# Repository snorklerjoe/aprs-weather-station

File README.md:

# aprs-weather-station
An APRS weather station with a transmitter designed from scratch

_(Slideshow with more info)_

For more information, see my [blog](https://www.hosticlefifer.com/blog/?show=14)!

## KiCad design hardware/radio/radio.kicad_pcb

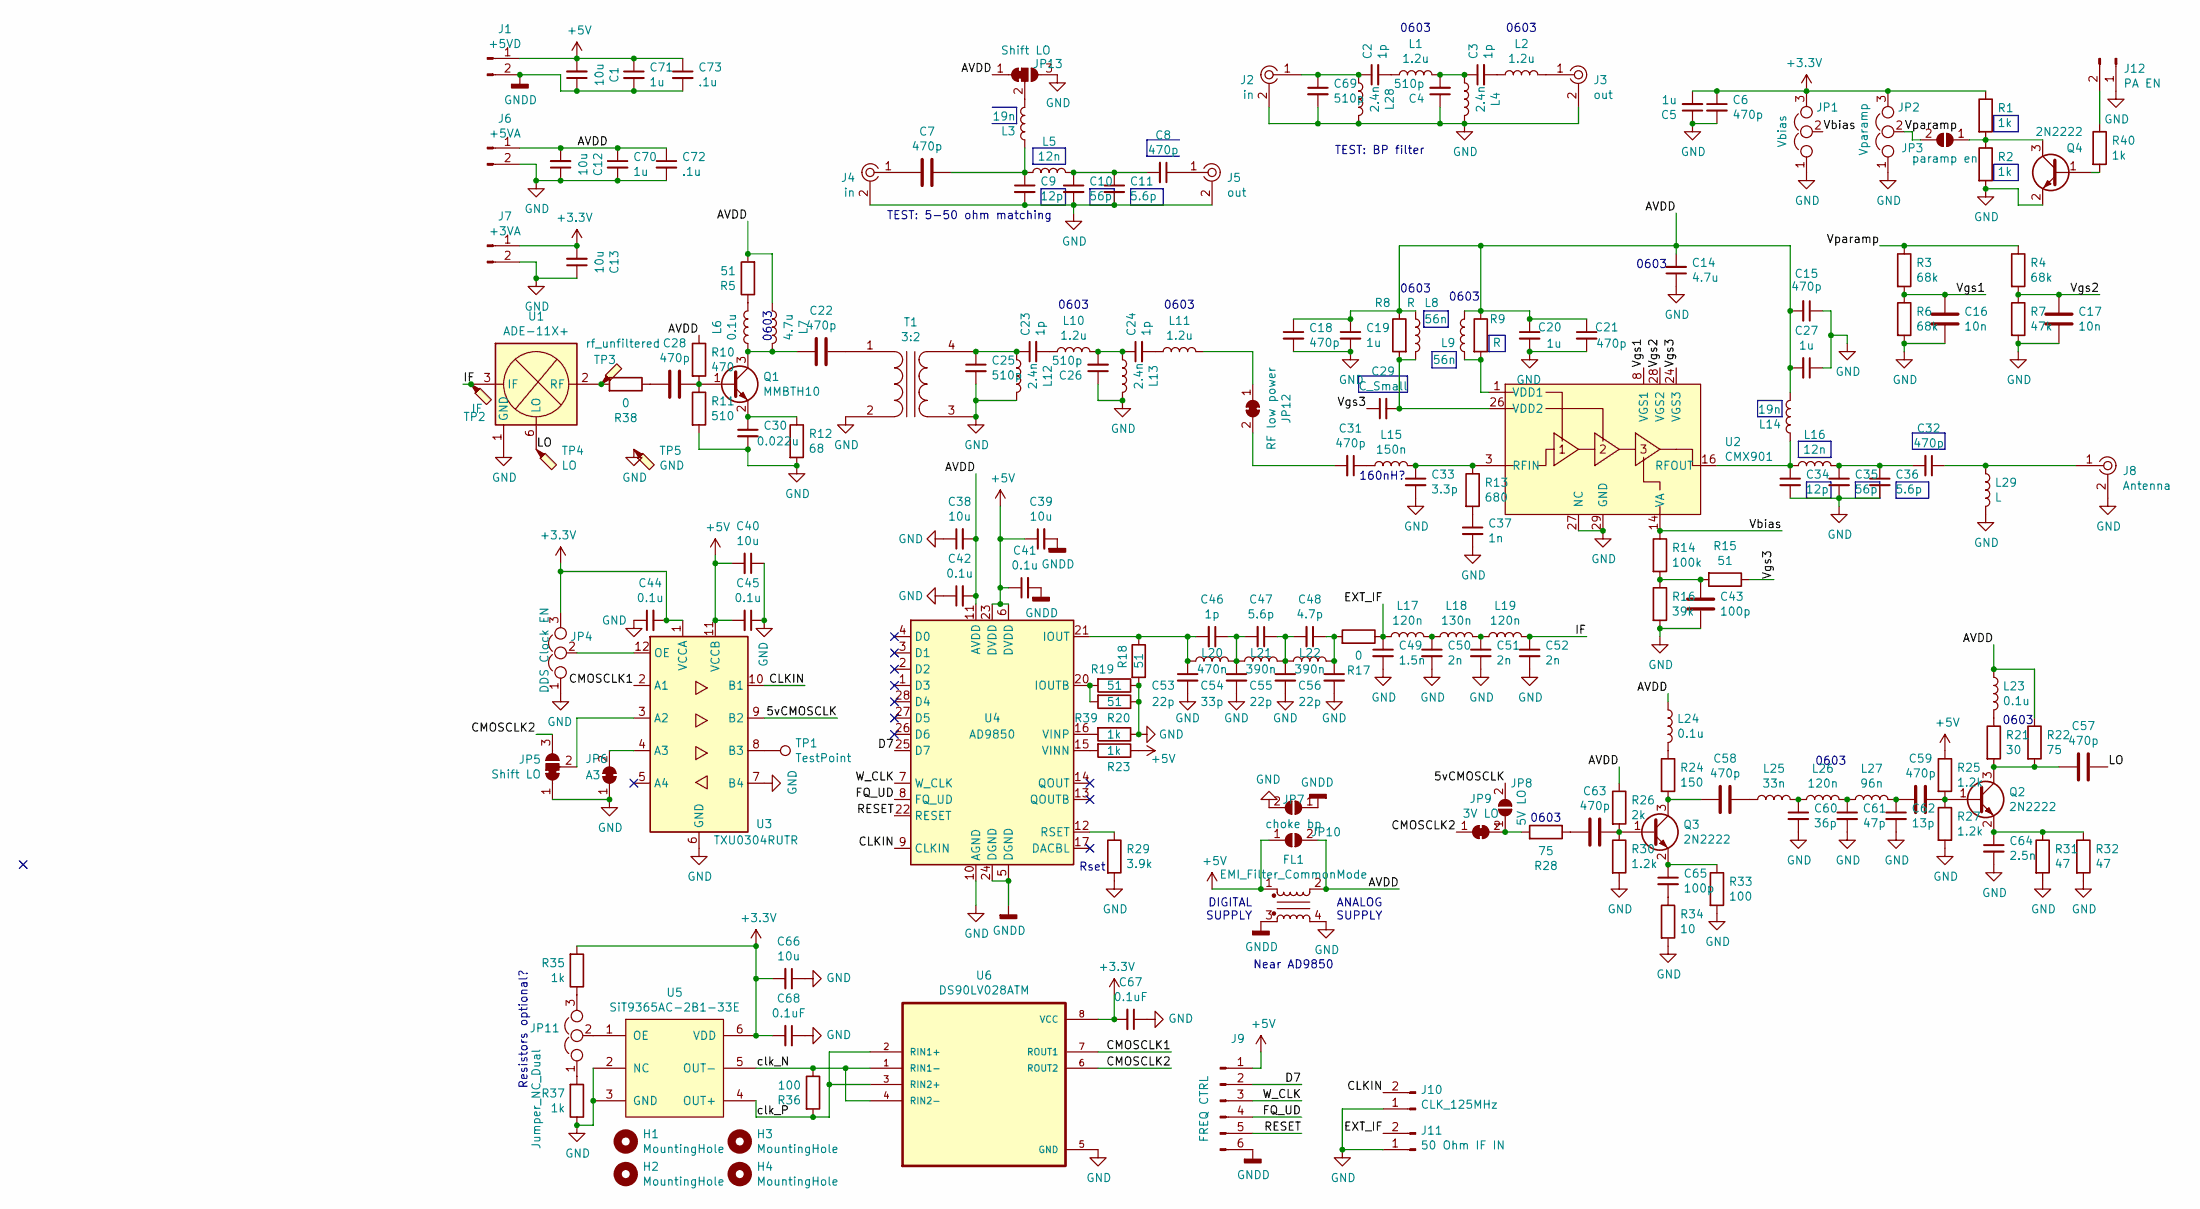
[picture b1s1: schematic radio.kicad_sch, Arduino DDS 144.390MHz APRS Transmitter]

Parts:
C1, C12, C13: 10u; C_0402_1005Metric
C2, C3, C23, C24, C46: 1p; C_0402_1005Metric
C4, C25, C26, C69: 510p; C_0402_1005Metric
C5, C19, C20, C27, C70, C71: 1u; C_0402_1005Metric
C6, C7, C8, C15, C18, C21, C22, C28, C31, C32, C57, C58, C59, C63: 470p; C_0402_1005Metric
C9, C34: 12p; C_0402_1005Metric
C10, C35: 56p; C_0402_1005Metric
C11, C36, C47: 5.6p; C_0402_1005Metric
C14: 4.7u; C_0603_1608Metric
C16, C17: 10n; C_0402_1005Metric
C29: C_Small; C_0402_1005Metric
C30: 0.022u; C_0402_1005Metric
C33: 3.3p; C_0402_1005Metric
C37: 1n; C_0402_1005Metric
C38, C39, C40, C66: 10u; C_0603_1608Metric
C41, C42, C44, C45: 0.1u; C_0402_1005Metric
C43, C65: 100p; C_0402_1005Metric
C48: 4.7p; C_0402_1005Metric
C49: 1.5n; C_0402_1005Metric
C50, C51, C52: 2n; C_0402_1005Metric
C53, C55, C56: 22p; C_0402_1005Metric
C54: 33p; C_0402_1005Metric
C60: 36p; C_0402_1005Metric
C61: 47p; C_0402_1005Metric
C62: 13p; C_0402_1005Metric
C64: 2.5n; C_0402_1005Metric
C67, C68: 0.1uF; C_0402_1005Metric
C72, C73: .1u; C_0402_1005Metric
FL1: EMI_Filter_CommonMode; common_mode_choke
H1, H2, H3, H4: MountingHole; MountingHole_3mm
J1: +5VD; PinHeader_1x02_P2.54mm_Vertical
J2, J4: in; RF_SMA_BoardEdge_142-0701-801; MPN 142-0701-801; Digi-Key_PN J502-ND
J3, J5: out; RF_SMA_BoardEdge_142-0701-801; MPN 142-0701-801; Digi-Key_PN J502-ND
J6: +5VA; PinHeader_1x02_P2.54mm_Vertical
J7: +3VA; PinHeader_1x02_P2.54mm_Vertical
J8: Antenna; RF_SMA_BoardEdge_142-0701-801; MPN 142-0701-801; Digi-Key_PN J502-ND
J9: FREQ CTRL; PinHeader_1x06_P2.54mm_Vertical
J10: CLK_125MHz; PinHeader_1x02_P2.54mm_Vertical
J11: 50 Ohm IF IN; PinHeader_1x02_P2.54mm_Vertical
J12: PA EN; PinHeader_1x02_P2.54mm_Vertical
JP1: Vbias; PinHeader_1x03_P2.54mm_Vertical
JP2: Vparamp; PinHeader_1x03_P2.54mm_Vertical
JP3: paramp en; SolderJumper-2_P1.3mm_Open_RoundedPad1.0x1.5mm
JP4: DDS Clock EN; PinHeader_1x03_P2.54mm_Vertical
JP5, JP13: Shift LO; SolderJumper-3_P1.3mm_Bridged2Bar12_Pad1.0x1.5mm
JP6: A3; SolderJumper-2_P1.3mm_Bridged2Bar_Pad1.0x1.5mm
JP7, JP10: choke bp; SolderJumper-2_P1.3mm_Open_Pad1.0x1.5mm
JP8: 5V LO; SolderJumper-2_P1.3mm_Open_Pad1.0x1.5mm
JP9: 3V LO; SolderJumper-2_P1.3mm_Bridged2Bar_Pad1.0x1.5mm
JP11: Jumper_NC_Dual; PinHeader_1x03_P2.54mm_Vertical
JP12: RF low power; SolderJumper-2_P1.3mm_Bridged2Bar_Pad1.0x1.5mm
L1, L2, L10, L11: 1.2u; L_0603_1608Metric
L3, L14: 19n; L_0402_1005Metric
L4, L12, L13, L28: 2.4n; L_0402_1005Metric
L5, L16: 12n; L_0402_1005Metric
L6, L23, L24: 0.1u; L_0402_1005Metric
L7: 4.7u; L_0603_1608Metric
L8, L9: 56n; L_0603_1608Metric
L15: 150n; L_0402_1005Metric
L17, L19: 120n; L_0402_1005Metric
L18: 130n; L_0402_1005Metric
L20: 470n; L_0402_1005Metric
L21, L22: 390n; L_0402_1005Metric
L25: 33n; L_0402_1005Metric
L26: 120n; L_0603_1608Metric
L27: 96n; L_0402_1005Metric
L29: L; L_0805_2012Metric
Q1: MMBTH10; SOT-23
Q2, Q3, Q4: 2N2222; SOT-23
R1, R2, R20, R23, R35, R37, R40: 1k; R_0402_1005Metric
R3, R4, R6: 68k; R_0402_1005Metric
R5, R15, R18, R19, R39: 51; R_0402_1005Metric
R7: 47k; R_0402_1005Metric
R8, R9: R; R_0402_1005Metric
R10: 470; R_0402_1005Metric
R11: 510; R_0402_1005Metric
R12: 68; R_0402_1005Metric
R13: 680; R_0402_1005Metric
R14: 100k; R_0402_1005Metric
R16: 39k; R_0402_1005Metric
R17, R38: 0; R_0402_1005Metric
R21: 30; R_0603_1608Metric
R22, R28: 75; R_0603_1608Metric
R24: 150; R_0402_1005Metric
R25, R27, R30: 1.2k; R_0402_1005Metric
R26: 2k; R_0402_1005Metric
R29: 3.9k; R_0402_1005Metric
R31, R32: 47; R_0402_1005Metric
R33, R36: 100; R_0402_1005Metric
R34: 10; R_0402_1005Metric
T1: 3:2; Transformer_Toroid_Horizontal_D9.0mm_Amidon-T30
TP1: TestPoint; TestPoint_Pad_2.0x2.0mm
TP2: IF; TestPoint_Pad_2.0x2.0mm
TP3: rf_unfiltered; TestPoint_Pad_2.0x2.0mm
TP4: LO; TestPoint_Pad_2.0x2.0mm
TP5: GND; TestPoint_Pad_2.0x2.0mm
U1: ADE-11X+; Mini-Circuits_CD542_LandPatternPL-052
U2: CMX901; QFN-28_EP_5x5_Pitch0.5mm
U3: TXU0304RUTR; Texas_R_PUQFN-N12
U4: AD9850; SSOP-28_5.3x10.2mm_P0.65mm
U5: SiT9365AC-2B1-33E; POD-038-PQFD-006-C03225
U6: DS90LV028ATM; SOIC127P599X175-8N

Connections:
+3V3: C5.2, C6.1, C13.2, C44.2, C66.2, C67.2, C68.2, J7.1, JP1.3, JP2.3, JP4.3, R1.1, R35.2, U3.1 (VCCA), U5.6 (VDD), U6.8 (VCC)
+5V: C1.2, C39.1, C40.2, C41.1, C45.2, C71.1, C73.1, FL1.1, J1.1, J9.1, JP10.1 (A), R23.1, R25.1, U3.11 (VCCB), U4.6 (DVDD), U4.23 (DVDD)
/5vCMOSCLK: JP8.2 (B), U3.9 (B2)
/AVDD: C12.2, C14.2, C15.2, C18.1, C19.1, C20.1, C21.1, C27.2, C38.2, C42.2, C70.1, C72.1, FL1.2, J6.1, JP10.2 (B), JP13.1 (A), L7.1, L8.2, L9.2, L14.2, L23.1, L24.1, R5.2, R8.1, R9.1, R10.1, R22.1, R26.1, U4.11 (AVDD), U4.18 (AVDD)
/CLKIN: J10.2, U3.10 (B1), U4.9 (CLKIN)
/CMOSCLK1: U3.2 (A1), U6.7 (ROUT1)
/CMOSCLK2: JP5.3 (B), JP9.1 (A), U6.6 (ROUT2)
/D7: J9.2, U4.25 (D7)
/EXT_IF: C49.1, J11.2, L17.1, R17.1
/FQ_UD: J9.4, U4.8 (FQ_UD)
/IF: C52.1, L19.2, TP2.1, U1.3 (IF)
/LO: C57.1, TP4.1, U1.6 (LO)
/RESET: J9.5, U4.22 (RESET)
/Vbias: JP1.2, R14.1, U2.14 (VA)
/Vgs1: C16.1, R3.2, R6.1, U2.8 (VGS1)
/Vgs2: C17.1, R4.2, R7.1, U2.28 (VGS2)
/Vgs3: C29.1, R15.1, U2.24 (VGS3)
/Vparamp: JP2.2, JP3.2 (B), R3.1, R4.1
/W_CLK: J9.3, U4.7 (W_CLK)
/clk_N: R36.1, U5.5 (OUT-), U6.1 (RIN1-), U6.4 (RIN2-)
/clk_P: R36.2, U5.4 (OUT+), U6.2 (RIN1+), U6.3 (RIN2+)
GND: C4.1, C5.1, C6.2, C9.2, C10.2, C11.2, C12.1, C13.1, C14.1, C15.1, C16.2, C17.2, C18.2, C19.2, C20.2, C21.2, C25.2, C26.1, C27.1, C30.2, C33.2, C34.2, C35.2, C36.2, C37.2, C38.1, C40.1, C42.1, C43.2, C44.1, C45.1, C49.2, C50.2, C51.2, C52.2, C53.2, C54.2, C55.2, C56.2, C60.2, C61.2, C62.2, C64.2, C66.1, C67.1, C68.1, C69.2, C70.2, C72.2, FL1.4, J2.2, J3.2, J4.2, J5.2, J6.2, J7.2, J8.2, J10.1, J11.1, J12.1, JP1.1, JP2.1, JP4.1, JP5.1 (A), JP6.1 (A), JP7.2 (B), JP13.3 (B), L4.2, L12.2, L13.2, L28.2, L29.2, Q4.2 (E), R2.2, R6.2, R7.2, R11.2, R12.2, R16.2, R18.2, R19.1, R20.1, R27.2, R29.2, R30.2, R31.2, R32.2, R33.2, R34.2, R37.1, R39.1, T1.2 (AB), T1.3 (SA), TP5.1, U1.1 (GND), U1.4 (GND), U1.5 (GND), U2.2 (NC), U2.4 (NC), U2.6 (NC), U2.7 (NC), U2.9 (NC), U2.10 (NC), U2.11 (NC), U2.12 (NC), U2.13 (NC), U2.15 (NC), U2.21 (NC), U2.22 (NC), U2.23 (NC), U2.25 (NC), U2.27 (NC), U2.29 (GND), U3.6 (GND), U3.7 (B4), U4.10 (AGND), U4.19 (AGND), U5.2 (NC), U5.3 (GND), U6.5 (GND)
GNDD: C1.1, C39.2, C41.2, C71.2, C73.2, FL1.3, J1.2, J9.6, JP7.1 (A), U4.5 (DGND), U4.24 (DGND)
unnamed: C2.1, C69.1, J2.1, L28.1
unnamed: C2.2, L1.1
unnamed: C3.1, C4.2, L1.2, L4.1
unnamed: C3.2, L2.1
unnamed: C7.1, C9.1, L3.1, L5.1
unnamed: C7.2, J4.1
unnamed: C8.1, J5.1
unnamed: C8.2, C10.1, C11.1, L5.2
unnamed: C22.1, T1.1 (AA)
unnamed: C22.2, L6.1, L7.2, Q1.3 (C)
unnamed: C23.1, C25.1, L12.1, T1.4 (SB)
unnamed: C23.2, L10.1
unnamed: C24.1, C26.2, L10.2, L13.1
unnamed: C24.2, L11.1
unnamed: C28.1, Q1.1 (B), R10.2, R11.1
unnamed: C28.2, R38.1
unnamed: C29.2, L8.1, R8.2, U2.26 (VDD2)
unnamed: C30.1, Q1.2 (E), R12.1
unnamed: C31.1, L15.1
unnamed: C31.2, JP12.2 (B)
unnamed: C32.1, J8.1, L29.1
unnamed: C32.2, C35.1, C36.1, L16.2
unnamed: C33.1, L15.2, R13.1, U2.3 (RFIN), U2.5 (RFIN)
unnamed: C34.1, L14.1, L16.1, U2.16 (RFOUT), U2.17 (RFOUT), U2.18 (RFOUT), U2.19 (RFOUT), U2.20 (RFOUT)
unnamed: C37.1, R13.2
unnamed: C43.1, R14.2, R15.2, R16.1
unnamed: C46.1, C47.2, C54.1, L20.2, L21.1
unnamed: C46.2, C53.1, L20.1, R18.1, U4.21 (IOUT)
unnamed: C47.1, C48.2, C55.1, L21.2, L22.1
unnamed: C48.1, C56.1, L22.2, R17.2
unnamed: C50.1, L17.2, L18.1
unnamed: C51.1, L18.2, L19.1
unnamed: C57.2, Q2.3 (C), R21.2, R22.2
unnamed: C58.1, L25.1
unnamed: C58.2, Q3.3 (C), R24.2
unnamed: C59.1, Q2.1 (B), R25.2, R27.1
unnamed: C59.2, C62.1, L27.2
unnamed: C60.1, L25.2, L26.1
unnamed: C61.1, L26.2, L27.1
unnamed: C63.1, Q3.1 (B), R26.2, R30.1
unnamed: C63.2, R28.1
unnamed: C64.1, Q2.2 (E), R31.1, R32.1
unnamed: C65.1, Q3.2 (E), R33.1
unnamed: C65.2, R34.1
unnamed: J3.1, L2.2
unnamed: J12.2, R40.1
unnamed: JP3.1 (A), Q4.3 (C), R1.2, R2.1
unnamed: JP4.2, U3.12 (OE)
unnamed: JP5.2 (C), U3.3 (A2)
unnamed: JP6.2 (B), U3.4 (A3)
unnamed: JP8.1 (A), JP9.2 (B), R28.2
unnamed: JP11.1, R37.2
unnamed: JP11.2, U5.1 (OE)
unnamed: JP11.3, R35.1
unnamed: JP12.1 (A), L11.2
unnamed: JP13.2 (C), L3.2
unnamed: L6.2, R5.1
unnamed: L9.1, R9.2, U2.1 (VDD1)
unnamed: L23.2, R21.1
unnamed: L24.2, R24.1
unnamed: Q4.1 (B), R40.2
unnamed: R19.2, R39.2, U4.20 (IOUTB)
unnamed: R20.2, U4.16 (VINP)
unnamed: R23.2, U4.15 (VINN)
unnamed: R29.1, U4.12 (RSET)
unnamed: R38.2, TP3.1, U1.2 (RF)
unnamed: TP1.1, U3.8 (B3)

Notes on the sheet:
0603
TEST: 5-50 ohm matching
Near AD9850
DIGITAL SUPPLY
Rset
0603
TEST: BP filter
ANALOG SUPPLY
160nH?
Resistors optional?

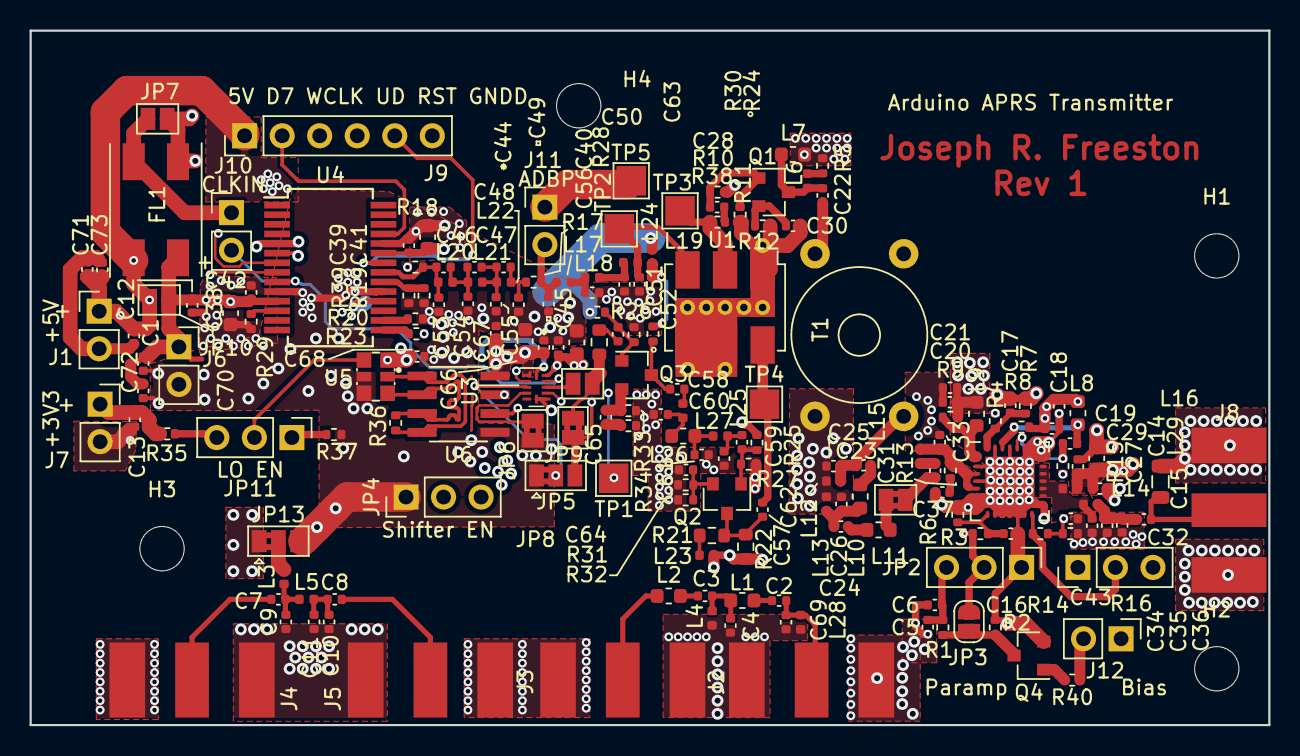
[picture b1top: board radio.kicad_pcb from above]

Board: 4 copper layers, 83.8 x 47.0 mm, 188 parts (0 on the bottom side), 90 nets.

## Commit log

2022-12-28 Initial commit... (Starting the use of GIT for this project) Project began in September 2021
2022-12-29 Removing oversized FFT files
2022-12-29 Set hardware files as detectable by linguist
2022-12-29 Created readme assets folder
